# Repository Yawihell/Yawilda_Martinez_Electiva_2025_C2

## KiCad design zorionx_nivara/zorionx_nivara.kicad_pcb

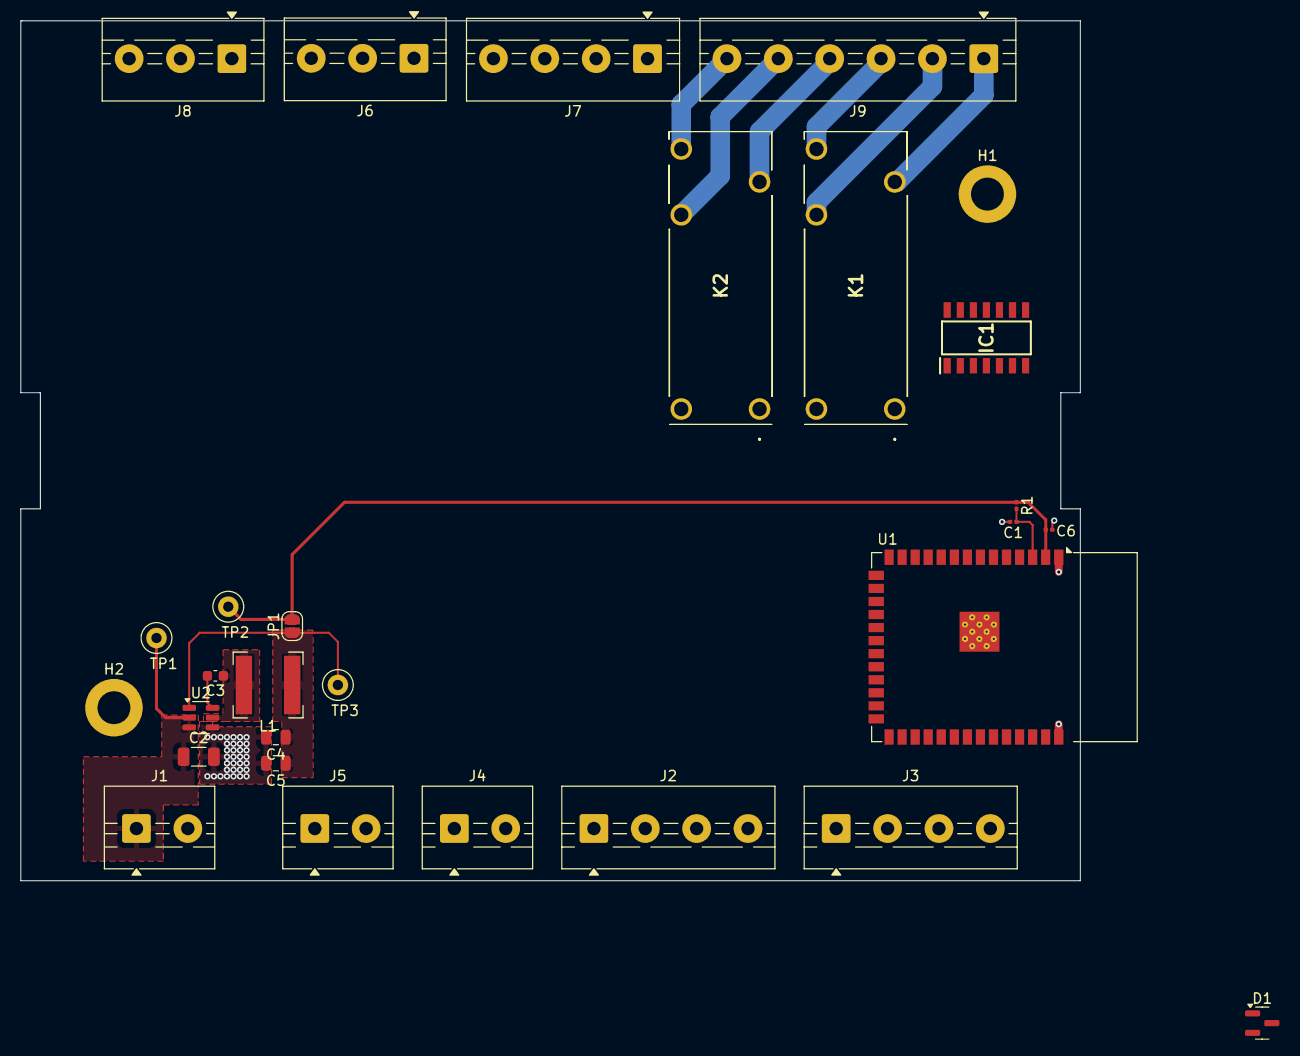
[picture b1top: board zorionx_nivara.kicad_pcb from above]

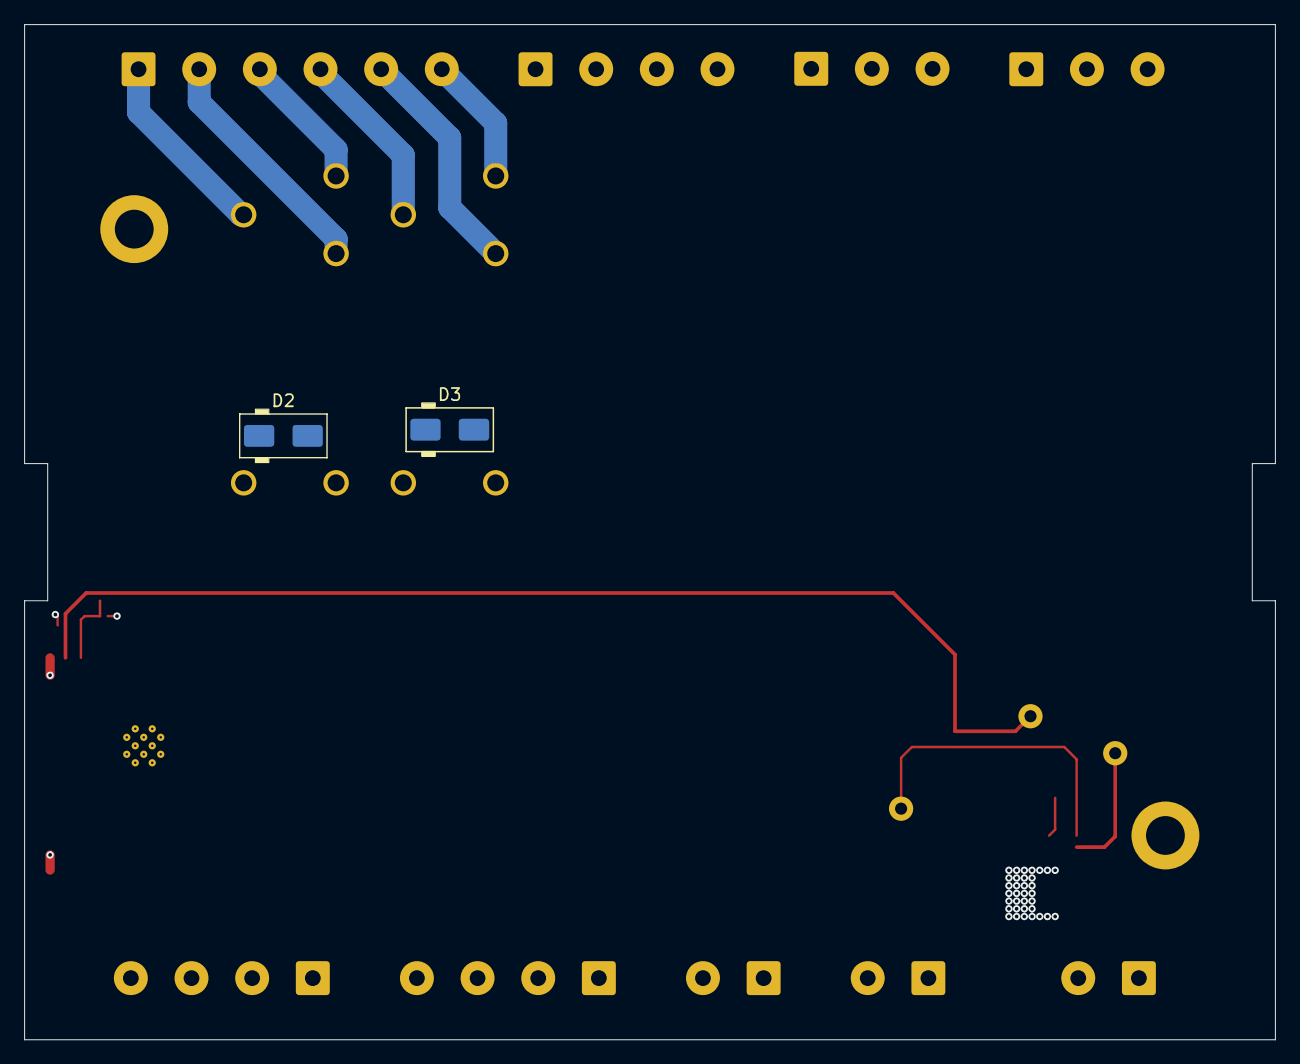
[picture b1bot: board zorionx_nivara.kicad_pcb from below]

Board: 4 copper layers, 103.1 x 83.7 mm, 31 parts (2 on the bottom side), 15 nets.

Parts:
C1: 1uf; C_0201_0603Metric
C2: 10uf; C_1206_3216Metric
C3: .1uf; C_0603_1608Metric
C4, C5: 22uf; C_0805_2012Metric
C6: .1uf; C_0201_0603Metric
D1: SM712_SOT23; SOT-23
D2, D3: M7; D_SMA
H1, H2: MountingHole_Pad_MP; MountingHole_3.2mm_M3_DIN965_Pad
IC1: BTS723GW; SOIC127P600X175-14N
J1, J4, J5: Screw_Terminal_01x02; TerminalBlock_MaiXu_MX126-5.0-02P_1x02_P5.00mm
J2, J3, J7: Screw_Terminal_01x04; TerminalBlock_MaiXu_MX126-5.0-04P_1x04_P5.00mm
J6, J8: Screw_Terminal_01x03; TerminalBlock_MaiXu_MX126-5.0-03P_1x03_P5.00mm
J9: Screw_Terminal_01x06; TerminalBlock_MaiXu_MX126-5.0-06P_1x06_P5.00mm
JP1: SolderJumper_2_Open; SolderJumper-2_P1.3mm_Open_RoundedPad1.0x1.5mm
K1, K2: G6RL-1_DC24; G6RL1DC24
L1: L_Iron; L_Bourns-SRN6028
R1: R_US; R_0201_0603Metric
TP1, TP2, TP3: TestPoint; TestPoint_Loop_D1.80mm_Drill1.0mm_Beaded
U1: ESP32-S3-WROOM-1
U2: AP63203WU; TSOT-23-6

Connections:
+3.3V: C6.2, JP1.2 (B), R1.1, TP2.1, U1.2 (3V3)
/board_zorionx-nivara/RLY1_C: J9.1, K1.2 (COM)
/board_zorionx-nivara/RLY1_NC: J9.2, K1.4 (NC)
/board_zorionx-nivara/RLY1_NO: J9.3, K1.3 (NO)
/board_zorionx-nivara/RLY2_C: J9.4, K2.2 (COM)
/board_zorionx-nivara/RLY2_NC: J9.5, K2.4 (NC)
/board_zorionx-nivara/RLY2_NO: J9.6, K2.3 (NO)
GND: C1.2, C2.2, C4.2, C5.2, C6.1, D2.2 (A), D3.2 (A), IC1.4 (GND), J1.2, J3.1, J5.1, J6.3, J8.3, K1.5 (COIL_2), K2.5 (COIL_2), U1.1 (GND), U1.40 (GND), U1.41 (GND), U2.4 (GND)
unnamed: D2.1 (K), IC1.12 (OUT1_1), IC1.13 (OUT1_2), K1.1 (COIL_1)
unnamed: D3.1 (K), IC1.9 (OUT2_1), IC1.10 (OUT2_2), K2.1 (COIL_1)
unnamed: C4.1, C5.1, JP1.1 (A), L1.2, TP3.1, U2.1 (FB)
unnamed: C1.1, R1.2, U1.3 (EN)
unnamed: C3.2, U2.6 (BST)
unnamed: C3.1, L1.1, U2.5 (SW)
VCC: C2.1, IC1.1 (VBB_1), IC1.7 (VBB_2), IC1.8 (VBB_3), IC1.14 (VBB_4), J1.1, TP1.1, U2.2 (EN), U2.3 (IN)

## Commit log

2025-05-30 Tarea 2 Freecad
2025-06-13 Tapa tarea 2 solidegde
2025-07-30 Tarea 2 completa
2025-08-15 Esquemas Tarea 3
2025-08-17 tarea 5 kicad
2025-08-18 zorionx-nivara esquema iniciado
2025-08-20 ruteo power
2025-08-20 driver relay
